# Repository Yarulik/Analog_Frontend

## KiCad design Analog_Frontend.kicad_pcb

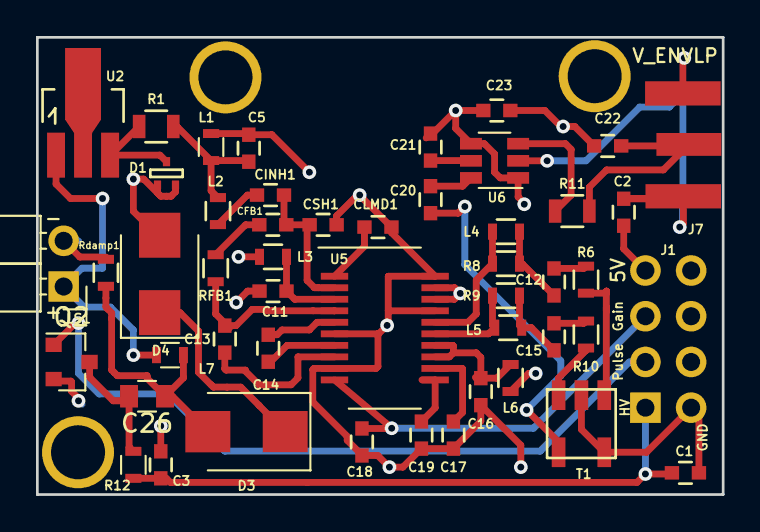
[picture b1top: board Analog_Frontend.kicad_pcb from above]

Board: 4 copper layers, 38.1 x 25.4 mm, 52 parts (1 on the bottom side), 36 nets.

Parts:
C1, C2, C3: 0.1u; C_0603
C5: 1n; C_0603
C11, C12, C13, C14, C15, C16, C17, C23: 0.1µF; C_0603
C18, C19: 1nF; C_0603
C20: 6.8nF; C_0603
C21: 2.2nF; C_0603
C22: 470pF; C_0603
C26: .01u; C_0805
CFB1: 18nF; C_0603
CINH1: 0.1µF; C_0603
CLMD1: 0.1µF; C_0603
CSH1: 22pF; C_0603
D1: BAV99T; SOT-523
D3, D4: BZX84C6V2L; D_SMB
J1: CONN_02X03; Pin_Header_Angled_2x04_Pitch2.54mm
J2, J4, J6: Screw_Terminal_1x01; SCREWM3
J7: CONN_COAXIAL; SAM8857-ND
L1: 1u; L_0603
L2, L3, L4, L5, L6: 120nH FB; R_0603
L7: .35u; L_0603
LS1: Piezo; Pin_Header_Angled_1x02_Pitch2.54mm
Q2: Q_NMOS_SDG; SOT-23
R1: 100; R_0805
R6, R10: 237; R_0603
R8, R9: 100; R_0603
R11: 68; R_0805
R12: 4.02; R_0603
RFB1: 274; R_0603
Rdamp1: 200; R_0603
T1: CX2041NLT
U2: MD0100N8; SOT89-3_Housing_Handsoldering
U5: AD8331; QSOP-20_3.9x8.6mm_Pitch0.64mm
U6: LTC5507; TSOT-23-6_MK06A

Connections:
+5V: C2.1, C21.2, C23.1, J1.7, L3.1, L6.2, U5.18, U5.19, U6.1, U6.4
/PCAP: C21.1, U6.5
/PULSE: J1.3, Q2.3
/RFin: C20.2, U6.6
/VCM: C19.1, U5.11
/VGA+: L5.1, R9.2, U5.15
/VGA-: L4.1, R8.2, U5.16
/VGA_PWR: C16.1, L6.1, U5.13, U5.14
/V_ENVLP: C22.1, J7.1, R11.2
/Vpiezo: L7.2, LS1.1, U2.1
GAIN: C18.1, J1.5, U5.10
GND: C1.2, C2.2, C3.2, C5.2, C11.2, C16.2, C17.2, C18.2, C19.2, C22.2, C23.2, CLMD1.1, CSH1.2, D1.1, D1.2, D4.2, J1.2, J1.4, J1.6, J1.8, J7.2, L1.2, LS1.2, Q2.1, Rdamp1.2, T1.2, T1.5, U5.6, U5.9, U5.17, U5.20, U6.2
HV: C1.1, C3.1, J1.1, R12.1
unnamed: C11.1, L3.2, U5.3
unnamed: C12.1, L4.2, R8.1
unnamed: C12.2, R6.1
unnamed: C13.1, RFB1.2, U5.4
unnamed: C13.2, U5.8
unnamed: C14.1, U5.5
unnamed: C14.2, U5.7
unnamed: C15.1, L5.2, R9.1
unnamed: C15.2, R10.1
unnamed: C17.1, U5.12
unnamed: C26.1, D3.2, L7.1, Rdamp1.1
unnamed: C26.2, Q2.2, R12.2
unnamed: CFB1.1, CINH1.2, CSH1.1, U5.2
unnamed: CFB1.2, RFB1.1
unnamed: CINH1.1, L2.2
unnamed: CLMD1.2, U5.1
unnamed: D1.3, R1.2, U2.3
unnamed: D3.1, D4.1
unnamed: R6.2, T1.1
unnamed: R10.2, T1.3
unnamed: R11.1, U6.3
V_VGA: C20.1, T1.4
Vfiltered: C5.1, L1.1, L2.1, R1.1

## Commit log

2018-05-24 Add 4_layer PCB design for 2.2_op1
2018-05-29 4 layer boarad for 2.2.3
2018-05-30 update to 2.2.3 4 layer
2018-06-06 some minor change
2018-06-06 4 layer 2.2.1
2018-08-16 Rename Analog_Frontend.kicad_pcb.orig to Analog_Frontend_2_Layer.kicad_pcb
    Adjusted name for the 2-layer original version
2018-08-16 Rename Analog_Frontend.kicad_pcb to Analog_Frontend_4_Layer.kicad_pcb
    Added "4-Layer" to the file name to distinct from the 2-layer 2.2.1 PCB.
2018-08-16 Rename Analog_Frontend.kicad_pcb to Analog_Frontend_4_Layer.kicad_pcb
2018-08-16 Rename Analog_Frontend.kicad_pcb.orig to Analog_Frontend_2_Layer.kicad_pcb.orig
2018-08-16 Rename Analog_Frontend_2_Layer.kicad_pcb.orig to Analog_Frontend_2_Layer.kicad_pcb
